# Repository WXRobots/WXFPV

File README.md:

# WXFPV
A FPV project for BF &amp; INAV

It include 2 parts for now：
Core Board and Main Board

## Core Board

Core Board is an exchangeable part to apply different MCUs for your ESC，such as AT32F421G8U7，EFM8BB21F16I etc.
The size of this circuit board is fully compatible with mtbsk8's design.
(https://oshwhub.com/mtbsk8/ji-yu-blheli-gu-jian-de-si-he-yi-wu-shua-dian-ji-dian-diao-esc-30-5mm-ban-ben)

EFM8BB21F16I's version can use BLHeli_S firmware
AT32F421G8U7's version can use AM32 firmare

## Main Board

Main Board is an 2-in-1 board，it include a flight controller and a 4-in-1 ESC in One Board.
It is designed to allow for splitting into two pieces for use,for better flexibility,replaceability and maintainability
It can use STM32F405RGT6 or APM32F405RGT6

It is additionally designed with 2 servo PWM interfaces and 3 high-power LED interfaces，so you can connect your servo or filament(or anything you want)to it

In the next upgrade,it will be 3-in-1，added by a communication module

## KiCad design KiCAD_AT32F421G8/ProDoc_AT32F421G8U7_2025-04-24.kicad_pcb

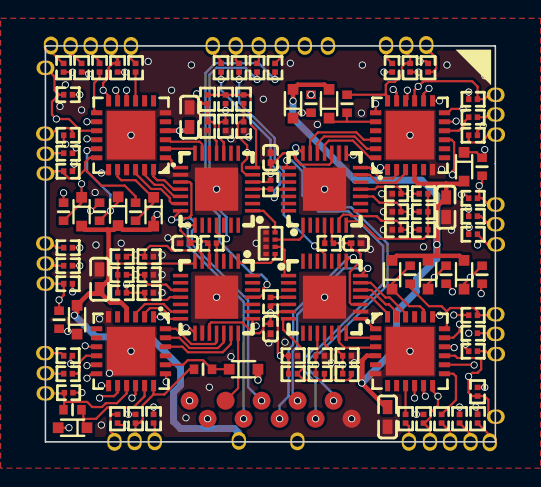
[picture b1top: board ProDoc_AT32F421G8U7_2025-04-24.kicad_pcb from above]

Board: 4 copper layers, 25.0 x 22.0 mm, 119 parts (0 on the bottom side), 111 nets.

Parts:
C1, C6, C11, C16: C0201
C3, C4, C5, C8, C9, C10, C13, C14, C15, C18, C19, C20, C29, C30, C31, C32: C0402
D1, D2, D3, D4, D5, D6, D7, D8, D9, D10, D11, D12: SOD-523_L1.2-W0.8-LS1.6-FD
R1, R4, R5, R6, R7, R8, R9, R10, R11, R12, R13, R14, R15, R16, R17, R18, R19, R21, R23, R24, R25, R26, R27, R28, R29, R30, R31, R32, R33, R34, R35, R36, R37, R39, R41, R42, R43, R44, R45, R46, R47, R48, R49, R50, R51, R52, R53, R54, R55, R58, R59, R60, R61, R62, R63, R64, R65, R66, R67, R68, R69, R70, R71, R72, R73, R74, R75, R76: R0201
RN1: RES-ARRAY-SMD_0201-8P-L1.4-W0.6-BL
TP1, TP2, TP3, TP4, TP5, TP6, TP7, TP8, TP9, TP10: Test-Point-0.5mm
U1, U3, U5, U7: VQFN-24_L4.0-W4.0-P0.50-TL-EP2.7
U2, U4, U6, U8: QFN-28_L4.0-W4.0-P0.40-TL-EP2.4

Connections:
3.3V: C1.2, C6.2, C11.2, C16.2, R73.1, R74.1, R75.1, R76.1, TP10.1, U2.5, U2.17, U4.5, U4.17, U6.5, U6.17, U8.5, U8.17
12V: C29.2, C30.2, C31.2, C32.2, D1.1, D2.1, D3.1, D4.1, D5.1, D6.1, D7.1, D8.1, D9.1, D10.1, D11.1, D12.1, U1.4, U3.4, U5.4, U7.4
$1N5017: R1.1, U2.25
$1N5688: R73.2, U2.4
$2N3149: R19.1, U4.25
$2N3240: R74.2, U4.4
$3N2377: R37.1, U6.25
$3N3106: R75.2, U6.4
$4N2377: R55.1, U8.25
$4N3105: R76.2, U8.4
BOOT1: RN1.5, U2.1
BOOT2: RN1.8, U4.1
BOOT3: RN1.6, U6.1
BOOT4: RN1.7, U8.1
GND: C1.1, C6.1, C11.1, C16.1, C29.1, C30.1, C31.1, C32.1, R16.1, R17.1, R18.1, R34.1, R35.1, R36.1, R52.1, R53.1, R54.1, R70.1, R71.1, R72.1, RN1.1, RN1.2, RN1.3, RN1.4, TP9.1, U1.6, U1.25, U2.16, U2.29, U3.6, U3.25, U4.16, U4.29, U5.6, U5.25, U6.16, U6.29, U7.6, U7.25, U8.16, U8.29
M1_AH: U1.22, U2.20
M1_AL: U1.1, U2.15
M1_BH: U1.23, U2.19
M1_BL: U1.2, U2.14
M1_CH: U1.24, U2.18
M1_CL: U1.3, U2.13
M1_HO1: R4.1, U1.19
M1_HO2: R5.1, U1.16
M1_HO3: R6.1, U1.13
M1_LO1: R7.1, U1.11
M1_LO2: R10.1, U1.10
M1_LO3: R15.1, U1.9
M1_SEN_A: R8.2, R9.1, R18.2, U2.6
M1_SEN_B: R11.2, R12.1, R17.2, U2.10
M1_SEN_C: R13.2, R14.1, R16.2, U2.11
M1_SEN_COM: R8.1, R11.1, R13.1, U2.7
M1_SWCLK: TP1.1, U2.22
M1_SWDIO: TP2.1, U2.21
M1_VB1: C3.1, D1.2, U1.20
M1_VB2: C4.1, D2.2, U1.17
M1_VB3: C5.1, D3.2, U1.14
M1_VS1: C3.2, R9.2, U1.18
M1_VS2: C4.2, R12.2, U1.15
M1_VS3: C5.2, R14.2, U1.12
M2_AH: U3.22, U4.20
M2_AL: U3.1, U4.15
M2_BH: U3.23, U4.19
M2_BL: U3.2, U4.14
M2_CH: U3.24, U4.18
M2_CL: U3.3, U4.13
M2_HO1: R21.1, U3.19
M2_HO2: R23.1, U3.16
M2_HO3: R24.1, U3.13
M2_LO1: R25.1, U3.11
M2_LO2: R26.1, U3.10
M2_LO3: R29.1, U3.9
M2_SEN_A: R27.2, R28.1, R36.2, U4.6
M2_SEN_B: R30.2, R31.1, R35.2, U4.10
M2_SEN_C: R32.2, R33.1, R34.2, U4.11
M2_SEN_COM: R27.1, R30.1, R32.1, U4.7
M2_SWCLK: TP3.1, U4.22
M2_SWDIO: TP4.1, U4.21
M2_VB1: C8.1, D4.2, U3.20
M2_VB2: C9.1, D5.2, U3.17
M2_VB3: C10.1, D6.2, U3.14
M2_VS1: C8.2, R28.2, U3.18
M2_VS2: C9.2, R31.2, U3.15
M2_VS3: C10.2, R33.2, U3.12
M3_AH: U5.22, U6.20
M3_AL: U5.1, U6.15
M3_BH: U5.23, U6.19
M3_BL: U5.2, U6.14
M3_CH: U5.24, U6.18
M3_CL: U5.3, U6.13
M3_HO1: R39.1, U5.19
M3_HO2: R41.1, U5.16
M3_HO3: R42.1, U5.13
M3_LO1: R43.1, U5.11
M3_LO2: R44.1, U5.10
M3_LO3: R49.1, U5.9
M3_SEN_A: R45.2, R46.1, R54.2, U6.6
M3_SEN_B: R47.2, R48.1, R53.2, U6.10
M3_SEN_C: R50.2, R51.1, R52.2, U6.11
M3_SEN_COM: R45.1, R47.1, R50.1, U6.7
M3_SWCLK: TP5.1, U6.22
M3_SWDIO: TP6.1, U6.21
M3_VB1: C13.1, D7.2, U5.20
M3_VB2: C14.1, D8.2, U5.17
M3_VB3: C15.1, D9.2, U5.14
M3_VS1: C13.2, R46.2, U5.18
M3_VS2: C14.2, R48.2, U5.15
M3_VS3: C15.2, R51.2, U5.12
M4_AH: U7.22, U8.20
M4_AL: U7.1, U8.15
M4_BH: U7.23, U8.19
M4_BL: U7.2, U8.14
M4_CH: U7.24, U8.18
M4_CL: U7.3, U8.13
M4_HO1: R58.1, U7.19
M4_HO2: R59.1, U7.16
M4_HO3: R60.1, U7.13
M4_LO1: R61.1, U7.11
M4_LO2: R62.1, U7.10
M4_LO3: R67.1, U7.9
M4_SEN_A: R63.2, R64.1, R72.2, U8.6
M4_SEN_B: R65.2, R66.1, R71.2, U8.10
M4_SEN_C: R68.2, R69.1, R70.2, U8.11
M4_SEN_COM: R63.1, R65.1, R68.1, U8.7
M4_SWCLK: TP7.1, U8.22
M4_SWDIO: TP8.1, U8.21
M4_VB1: C18.1, D10.2, U7.20
M4_VB2: C19.1, D11.2, U7.17
M4_VB3: C20.1, D12.2, U7.14
M4_VS1: C18.2, R64.2, U7.18
M4_VS2: C19.2, R66.2, U7.15
M4_VS3: C20.2, R69.2, U7.12

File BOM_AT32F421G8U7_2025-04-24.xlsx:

No. | Quantity | Comment | Designator | Footprint | Value | Manufacturer Part | Manufacturer | Supplier Part | Supplier
1 | 4 | 100nF | C1,C6,C11,C16 | C0201 | 100nF | GRM033R61E104KE14D | muRata(村田) | C76939 | LCSC
2 | 12 | 1uF | C3,C4,C5,C8,C9,C10,C13,C14,C15,C18,C19,C20 | C0402 | 1uF | CL05A105KA5NQNC | SAMSUNG(三星) | C52923 | LCSC
3 | 4 | 4.7uF | C29,C30,C31,C32 | C0402 | 4.7uF | CGA0402X5R475M250GT | HRE(芯声) | C6119795 | LCSC
4 | 12 | 1N4148WT | D1,D2,D3,D4,D5,D6,D7,D8,D9,D10,D11,D12 | SOD-523_L1.2-W0.8-LS1.6-FD |  | 1N4148WT | WPMtek(维攀微) | C2688234 | LCSC
5 | 4 | 220Ω | R1,R19,R37,R55 | R0201 | 220Ω | RC0201FR-07220RL | YAGEO(国巨) | C274342 | LCSC
6 | 24 | 4.7Ω | R4,R5,R6,R7,R10,R15,R21,R23,R24,R25,R26,R29,R39,R41,R42,R43,R44,R49,R58,R59,R60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 | R0201 | 4.7Ω | 0201WMJ047JTEE | UNI-ROYAL(厚声) | C473492 | LCSC
7 | 28 | 10kΩ | R8,R9,R11,R12,R13,R14,R27,R28,R30,R31,R32,R33,R45,R46,R47,R48,R50,R51,R63,R64,R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 | R0201 | 10kΩ | 0201WMF1002TEE | UNI-ROYAL(厚声) | C473048 | LCSC
8 | 12 | 1kΩ | R16,R17,R18,R34,R35,R36,R52,R53,R54,R70,R71,R72 | R0201 | 1kΩ | 0201WMF1001TEE | UNI-ROYAL(厚声) | C270365 | LCSC
9 | 1 | 10kΩ | RN1 | RES-ARRAY-SMD_0201-8P-L1.4-W0.6-BL | 10kΩ | 4F01WMJ0103TEE | UNI-ROYAL(厚声) | C2769814 | LCSC
10 | 10 | Test-Point | TP1,TP2,TP3,TP4,TP5,TP6,TP7,TP8,TP9,TP10 | Test-Point-0.5mm
11 | 4 | JSM6288Q | U1,U3,U5,U7 | VQFN-24_L4.0-W4.0-P0.50-TL-EP2.7 |  | JSM6288Q | JSMSEMI(杰盛微) | C19077370 | LCSC
12 | 4 | AT32F421G8U7 | U2,U4,U6,U8 | QFN-28_L4.0-W4.0-P0.40-TL-EP2.4 |  | AT32F421G8U7 | ARTERY(雅特力) | C2765098 | LCSC

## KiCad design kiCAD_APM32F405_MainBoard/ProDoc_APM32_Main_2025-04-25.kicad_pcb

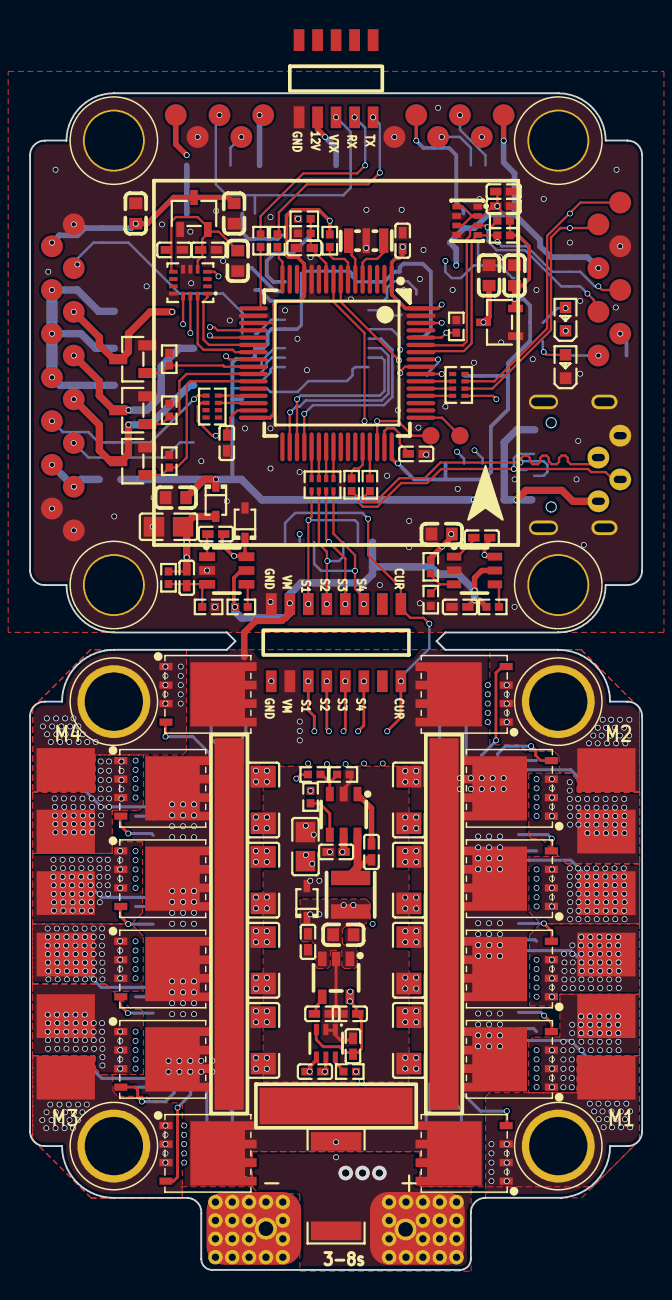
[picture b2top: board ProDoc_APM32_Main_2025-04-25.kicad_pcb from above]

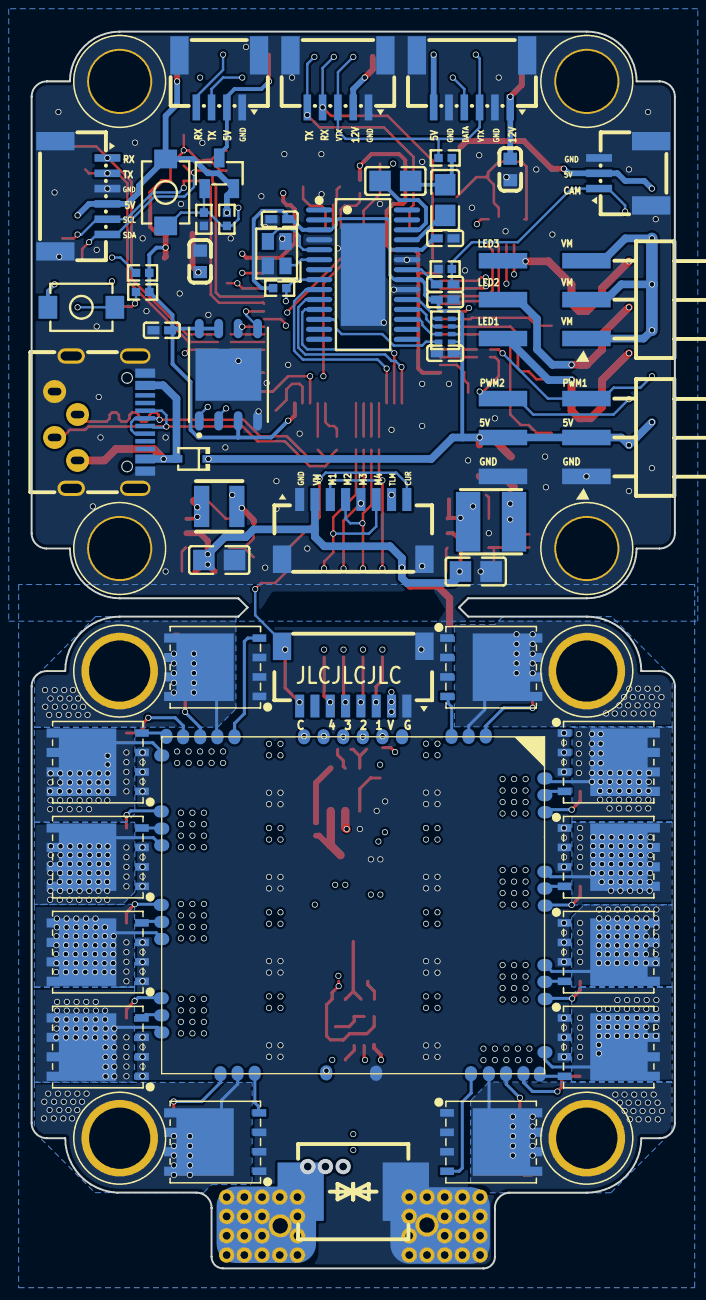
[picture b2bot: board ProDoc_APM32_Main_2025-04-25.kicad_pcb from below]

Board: 6 copper layers, 42.0 x 80.8 mm, 194 parts (59 on the bottom side), 136 nets.

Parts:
AT7456E1: TSSOP-28_L9.7-W4.4-P0.65-LS6.4-BL-EP-2
C18, C19, C20, C27, C28, C29, C30, C32, C41, C44, C45, C48, C49, C50, C51, C52, C53, C54, C55, C56, C57, C58, C61, C63, C66: C0402
C33, C38, C40, C42, C43, C62, C68, C69, C78, C79: C0603
C46, C47, C60, C64, C65, C67: C0805
C70, C71, C72, C73, C74, C75, C76, C77: C1206
CN1, CN2: CONN-SMD_8P-P1.00_MXSH-1.0-08P-WT1-0-A
D1, D2, D6: SOD-323_L1.7-W1.3-LS2.5-FD
D3: SOD-323_L1.7-W1.3-LS2.7-RD
H1: HDR-SMD_8P_P1.27-跨板连接排针
H2: HDR-SMD_5P_P1.27-跨板连接排针
L1, L2: IND-SMD_L3.0-W3.0-1
L3: IND-SMD_L4.0-W4.0_FNR40XXS
LED1, LED2: LED0603-RD
Q1, Q2, Q3, Q4, Q5, Q6, Q7, Q8, Q9, Q10, Q11, Q12, Q13, Q14, Q15, Q16, Q17, Q18, Q19, Q20, Q21, Q22, Q23, Q24: TDSON-8_L5.9-W5.2-P1.27-BL
Q25, Q26, Q56, Q57: SOT-23-3_L2.9-W1.3-P1.90-LS2.4-BR
R1, R2, R3, R4, R5, R6, R10, R11, R12, R13, R14, R15, R16, R17, R18, R19, R20, R28, R29, R30, R31, R108, R109, R110, R111, R112, R113, R114, R115, R116: R0402
RN1, RN2, RN3, RN4: RES-ARRAY-SMD_0402-8P-L2.0-W1.0-BL
SW1, SW2: KEY-SMD_L3.9-W3.0-LS5.0
TP1, TP2, TP3, TP4, TP5, TP6, TP7, TP8, TP10, TP12, TP14, TP16, TP17, TP19, TP20, TP21, TP22, TP23, TP24, TP25, TP26, TP27, TP29, TP30, TP31, TP32, TP33, TP34, TP35, TP36, TP38, TP40, TP41, TP42, TP43, TP44, TP45, TP46, TP47, TP48: Test-Point-0.5mm
U1: SC-70-6_L2.2-W1.3-P0.65-LS2.1-TL
U2: R2512
U3: LQFP-64_L10.0-W10.0-P0.50-LS12.0-BL
U4: SOT-23-5_L3.0-W1.7-P0.95-LS2.8-BR
U6, U55, U56: SOT-23-6_L2.9-W1.6-P0.95-LS2.8-BR
U8: BLHeli_四合一核心板_SJJ
U9: SMC_L6.9-W5.9-LS7.9-BI
U10, U11: SOT-23-3_L3.0-W1.7-P0.95-LS2.9-BR
U12: LGA-14_L3.0-W2.5-P0.50-BR
U13: OSC-SMD_4P-L2.0-W1.6-BL_X201624MKB4SI
U14: LGA-8_L2.5-W2.0-P0.65_AMP6127
U15: WSON-8_L6.0-W5.0-P1.27-BL-EP
U16, U54: CONN-SMD_6P-P1.00_MEGASTAR_ZX-SH1.0-6PWT
U17: CONN-SMD_5P-P1.00_MEGASTAR_ZX-SH1.0-5PWT
U18: CONN-SMD_3P-P1.00_MEGASTAR_ZX-SH1.0-3PWT
U19, U57: HDR-SMD_6P-P2.54-H-M-R2-C3-LS17.0
U53: CONN-SMD_4P-P1.00_MEGASTAR_ZX-SH1.0-4PWT
U58, U59: SMD-1_L25.0-W1.5
U60: SMD-2_L10.0-W2.0
USBC1: USB-C-SMD_KH-TYPE-C-16P
X1: OSC-SMD_3P-L3.2-W1.3-P1.2-L

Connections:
3V3: C27.1, C38.2, C48.1, C49.1, C51.1, R1.2, R2.2, R3.2, R4.2, R6.2, SW1.2, TP8.1, U3.1, U3.13, U3.19, U3.32, U3.48, U3.64, U10.2, U14.2, U14.6, U14.8, U15.3, U15.7, U15.8
3V3_GYRO: C43.2, C52.2, C53.2, U11.2, U12.5, U12.8
5V: AT7456E1.3, AT7456E1.21, AT7456E1.24, C40.2, C42.2, C54.2, C55.2, C56.2, C57.2, C68.2, C69.2, C78.2, D1.2, D2.2, Q56.2, R17.2, R108.2, RN4.5, RN4.6, RN4.7, RN4.8, SW2.1, TP16.1, TP20.1, TP24.1, TP26.1, TP29.1, U10.3, U11.3, U16.4, U18.2, U19.3, U19.4
12V: C28.2, C33.2, D3.1, L1.2, R30.2, U4.1, U4.3, U8.14
$1N5871: C20.1, U6.1
$1N5872: R29.2, U6.4
$1N5875: R30.1, R31.2, U6.3
$1N5876: C20.2, L1.1, U6.6
$1N5882: C29.2, U4.4
$3N1830: R28.1, U1.6
$4N5037: R6.1, U3.7
$4N5056: C45.1, U3.31
$4N5066: C41.1, U3.47
$4N5110: AT7456E1.6, U13.1
$4N5111: AT7456E1.5, U13.3
$4N5116: AT7456E1.22, C50.2
$4N5118: C46.2, C47.2, R16.1
$4N5119: AT7456E1.25, C47.1
$4N5120: AT7456E1.26, C46.1
$4N5162: LED2.2, R4.1
$4N5163: LED1.2, R1.1
$4N5203: RN1.3, U3.54
$4N5204: RN1.2, U3.53
$4N5218: R10.1, U3.16
$4N5219: R11.1, U3.17
$4N5327: AT7456E1.12, RN4.1
$4N5328: AT7456E1.17, RN4.2
$4N5329: AT7456E1.18, RN4.3
$4N5330: AT7456E1.19, RN4.4
$4N14776: C58.1, U55.1
$4N14777: R110.2, U55.4
$4N14780: R111.2, R112.1, U55.3
$4N14781: C58.2, L2.1, U55.6
$4N15508: C63.2, D6.2, L3.1, U56.6
$4N15513: C63.1, U56.1
$4N15879: R113.2, U56.4
$4N16265: C66.1, R114.2, R115.1, U56.3
+3.3V: C18.1, C30.2, U1.3, U4.5, U8.35
ADC_CUR: CN1.8, CN1.9, CN2.8, H1.1, R28.2, U3.9
ADC_VBAT: C44.1, R14.1, R15.2, U3.10
AH_1: Q1.4, U8.11
AH_2: Q7.4, U8.2
AH_3: Q13.4, U8.22
AH_4: Q19.4, U8.31
AL_1: Q2.4, U8.13
AL_2: Q8.4, U8.3
AL_3: Q14.4, U8.23
AL_4: Q20.4, U8.33
A_1: Q1.1, Q1.2, Q1.3, Q2.5, U8.12
A_2: Q7.1, Q7.2, Q7.3, Q8.5, U8.4
A_3: Q13.1, Q13.2, Q13.3, Q14.5, U8.24
A_4: Q19.1, Q19.2, Q19.3, Q20.5, U8.32
BH_1: Q3.4, U8.8
BH_2: Q9.4, U8.43
BH_3: Q15.4, U8.19
BH_4: Q21.4, U8.28
BIND: Q56.1, R108.1, R109.2, SW2.2, TP34.1
BL_1: Q4.4, U8.9
BL_2: Q10.4, U8.44
BL_3: Q16.4, U8.20
BL_4: Q22.4, U8.29
BOOT0: R5.1, SW1.1, TP7.1, U3.60
BOX_CS: U3.8, U15.1
BOX_MISO: U3.56, U15.2
BOX_MOSI: U3.57, U15.5
BOX_SCK: U3.55, U15.6
B_1: Q3.1, Q3.2, Q3.3, Q4.5, U8.10
B_2: Q9.1, Q9.2, Q9.3, Q10.5, U8.1
B_3: Q15.1, Q15.2, Q15.3, Q16.5, U8.21
B_4: Q21.1, Q21.2, Q21.3, Q22.5, U8.30
CAM: C50.1, R18.2, TP22.1, U18.1
CH_1: Q5.4, U8.5
CH_2: Q11.4, U8.42
CH_3: Q17.4, U8.18
CH_4: Q23.4, U8.25
CL_1: Q6.4, U8.6
CL_2: Q12.4, U8.40
CL_3: Q18.4, U8.16
CL_4: Q24.4, U8.26
C_1: Q5.1, Q5.2, Q5.3, Q6.5, U8.7
C_2: Q11.1, Q11.2, Q11.3, Q12.5, U8.41
C_3: Q17.1, Q17.2, Q17.3, Q18.5, U8.17
C_4: Q23.1, Q23.2, Q23.3, Q24.5, U8.27
D+: R13.2, TP5.1, USBC1.A6, USBC1.B6
D-: R12.2, TP3.1, USBC1.A7, USBC1.B7
DC_5V: C65.1, C66.2, D2.1, L3.2, R115.2
DM: R12.1, U3.44
DP: R13.1, U3.45
ELRS_5V: Q56.3, TP31.1, U53.2
ESC_S1: CN1.3, CN2.3, H1.6, RN2.8, U8.38
ESC_S2: CN1.4, CN2.4, H1.5, RN2.7, U8.39
ESC_S3: CN1.5, CN2.5, H1.4, RN2.6, U8.36
ESC_S4: CN1.6, CN2.6, H1.3, RN2.5, U8.37
GND: AT7456E1.4, AT7456E1.20, AT7456E1.23, AT7456E1.29, C18.2, C27.2, C28.1, C29.1, C30.1, C32.1, C33.1, C38.1, C40.1, C41.2, C42.1, C43.1, C44.2, C45.2, C48.2, C49.2, C51.2, C52.1, C53.1, C54.1, C55.1, C56.1, C57.1, C60.1, C61.1, C62.1, C64.1, C65.2, C67.1, C68.1, C69.1, C70.1, C71.1, C72.1, C73.1, C74.1, C75.1, C76.1, C77.1, C78.1, C79.1, CN1.1, CN1.10, CN2.1, CN2.9, CN2.10, D3.2, D6.1, H1.8, H2.1, LED1.1, Q2.1, Q2.2, Q2.3, Q4.1, Q4.2, Q4.3, Q6.1, Q6.2, Q6.3, Q8.1, Q8.2, Q8.3, Q10.1, Q10.2, Q10.3, Q12.1, Q12.2, Q12.3, Q14.1, Q14.2, Q14.3, Q16.1, Q16.2, Q16.3, Q18.1, Q18.2, Q18.3, Q20.1, Q20.2, Q20.3, Q22.1, Q22.2, Q22.3, Q24.1, Q24.2, Q24.3, Q25.2, Q26.2, Q57.2, R5.2, R15.1, R18.1, R19.1, R20.1, R31.1, R109.1, R111.1, R114.1, R116.1, TP6.1, TP14.1, TP17.1, TP23.1, TP30.1, TP35.1, TP46.1, U1.1, U1.2, U3.12, U3.18, U3.63, U4.2, U6.2, U8.15, U9.1, U10.1, U11.1, U12.6, U12.7, U12.11, U13.2, U13.4, U14.1, U14.5, U14.7, U15.4, U15.9, U16.3, U16.7, U16.8, U17.1, U17.6, U17.7, U18.3, U18.4, U18.5, U19.1, U19.2, U53.1, U53.5, U53.6, U54.2, U54.5, U54.7, U54.8, U55.2, U56.2, USBC1.1, USBC1.2, USBC1.3, USBC1.4, USBC1.A1, USBC1.A12, USBC1.B1, USBC1.B12, X1.2
GYRO1_CS: U3.20, U12.12
GYRO1_EXTI: U3.24, U12.4
I2C1_SCL: R2.1, TP19.1, U3.58, U14.4, U16.5
I2C1_SDA: R3.1, TP21.1, U3.59, U14.3, U16.6
LED: LED2.1, U3.62
LED1_GATE: Q25.1, R19.2, U3.27
LED1_OUT: Q25.3, TP42.1, U57.2
LED2_GATE: Q26.1, R20.2, U3.26
LED2_OUT: Q26.3, TP43.1, U57.4
LED3_GATE: Q57.1, R116.2, U3.25
LED3_OUT: Q57.3, TP44.1, U57.6
MOTOR1: RN2.1, U3.37
MOTOR2: RN2.2, U3.38
MOTOR3: RN2.3, U3.39
MOTOR4: RN2.4, U3.40
MOTOR7: RN3.5, U3.29
MOTOR8: RN3.6, U3.30
OSC_IN: U3.5, X1.3
OSC_OUT: U3.6, X1.1
OSD_CS: AT7456E1.8, R17.1, TP4.1, U3.46
PWM1: RN3.4, TP25.1, U19.5
PWM2: RN3.3, TP27.1, U19.6
SPI1_SCK: U3.21, U12.13
SPI1_SDI: U3.22, U12.1
SPI1_SDO: U3.23, U12.14
SPI2_SCK: AT7456E1.10, U3.34
SPI2_SDI: AT7456E1.11, U3.35
SPI2_SDO: AT7456E1.9, U3.36
SWCLK: TP1.1, U3.49
TLM: CN2.7, RN1.8
UART2_RX: H2.4, R11.2, TP33.1, U17.4, U53.4
UART2_TX: H2.5, R10.2, TP32.1, U17.5, U53.3
UART3_RX: RN1.1, U3.52
UART5_RX: RN1.6, TP10.1, U16.1
UART5_TX: RN1.7, TP12.1, U16.2
USB_5V: D1.1, TP2.1, USBC1.A4, USBC1.A9, USBC1.B4, USBC1.B9
VBAT: C19.1, U1.4, U2.1, U9.2
VM: C19.2, C32.2, C60.2, C61.2, C64.2, C67.2, C70.2, C71.2, C72.2, C73.2, C74.2, C75.2, C76.2, C77.2, CN1.2, CN2.2, H1.7, Q1.5, Q3.5, Q5.5, Q7.5, Q9.5, Q11.5, Q13.5, Q15.5, Q17.5, Q19.5, Q21.5, Q23.5, R14.2, R29.1, R110.1, R113.1, TP45.1, TP47.1, TP48.1, U1.5, U2.2, U6.5, U55.5, U56.5, U57.1, U57.3, U57.5, U58.1, U59.1, U60.1
VTX: H2.3, R16.2, TP38.1, U17.3, U54.3
VTX_5VOUT: TP40.1, U54.6
VTX_12V: C62.2, C79.2, H2.2, L2.2, R112.2, TP41.1, U17.2, U54.1
VTX_RX: TP36.1, U54.4

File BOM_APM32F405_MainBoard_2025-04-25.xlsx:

No. | Quantity | Comment | Designator | Footprint | Value | Manufacturer Part | Manufacturer | Supplier Part | Supplier
1 | 1 | AT7456E | AT7456E1 | TSSOP-28_L9.7-W4.4-P0.65-LS6.4-BL-EP-2 |  | AT7456E | 杭州中科微 | C82351 | LCSC
2 | 17 | 100nF | C18,C20,C27,C32,C44,C48,C49,C50,C51,C53,C54,C55,C56,C57,C58,C61,C63 | C0402 | 100nF | CL05B104KB54PNC | SAMSUNG(三星) | C307331 | LCSC
3 | 1 | 1nF | C19 | C0402 | 1nF | 0402B102K500NT | FH(风华) | C1523 | LCSC
4 | 1 | 1uF | C28 | C0402 | 1uF | CL05A105KA5NQNC | SAMSUNG(三星) | C52923 | LCSC
5 | 1 | 100pF | C29 | C0402 | 100pF | 0402CG101J500NT | FH(风华) | C1546 | LCSC
6 | 3 | 2.2uF | C30,C41,C45 | C0402 | 2.2uF | CL05A225MQ5NSNC | SAMSUNG(三星) | C12530 | LCSC
7 | 7 | 10uF | C33,C38,C40,C42,C43,C62,C79 | C0603 | 10uF | CL10A106MA8NRNC | SAMSUNG(三星) | C96446 | LCSC
8 | 3 | 22uF | C46,C47,C65 | C0805 | 22uF | CL21A226MAQNNNE | SAMSUNG(三星) | C45783 | LCSC
9 | 1 | 10nF | C52 | C0402 | 10nF | CL05B103KB5NNNC | SAMSUNG(三星) | C15195 | LCSC
10 | 3 | 4.7uF | C60,C64,C67 | C0805 | 4.7uF | CL21A475KBQNNNE | SAMSUNG(三星) | C98192 | LCSC
11 | 1 | 22pF | C66 | C0402 | 22pF | 0402CG220J500NT | FH(风华) | C1555 | LCSC
12 | 3 | 10uF | C68,C69,C78 | C0603 | 10uF | CL10A106KP8NNNC | SAMSUNG(三星) | C19702 | LCSC
13 | 8 | 10uF | C70,C71,C72,C73,C74,C75,C76,C77 | C1206 | 10uF | CL31A106KBHNNNE | SAMSUNG(三星) | C13585 | LCSC
14 | 2 | MXSH-1.0-08P-WT1-0-A | CN1,CN2 | CONN-SMD_8P-P1.00_MXSH-1.0-08P-WT1-0-A |  | MXSH-1.0-08P-WT1-0-A | MAX(迈旭) | C19185711 | LCSC
15 | 3 | B5819WS | D1,D2,D6 | SOD-323_L1.7-W1.3-LS2.5-FD |  | B5819WS | 宏迦橙 | C7420331 | LCSC
16 | 1 | SD12 | D3 | SOD-323_L1.7-W1.3-LS2.7-RD |  | SD12 | MDD | C502528 | LCSC
17 | 1 | HDR-SMD_8P_P1.27_跨板连接排针 | H1 | HDR-SMD_8P_P1.27-跨板连接排针
18 | 1 | OPTO | H2 | HDR-SMD_5P_P1.27-跨板连接排针
19 | 2 | 10uH | L1,L2 | IND-SMD_L3.0-W3.0-1 | 10uH | CKCSA3010-10uH/M | CENKER(岑科) | C5125973 | LCSC
20 | 1 | 10uH | L3 | IND-SMD_L4.0-W4.0_FNR40XXS | 10uH | MAI4020S-100MT | ceaiya(柯爱亚) | C520273 | LCSC
21 | 1 | PWR | LED1 | LED0603-RD |  | KT-0603R | KENTO | C2286 | LCSC
22 | 1 | LED | LED2 | LED0603-RD |  | NCD0603Y1 | 国星光电 | C84268 | LCSC
23 | 24 | HYG011N04LS2C2 | Q1,Q2,Q3,Q4,Q5,Q6,Q7,Q8,Q9,Q10,Q11,Q12,Q13,Q14,Q15,Q16,Q17,Q18,Q19,Q20,Q21,Q22,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 | TDSON-8_L5.9-W5.2-P1.27-BL |  | HYG011N04LS2C2 |  | C9900088765 | LCSC
24 | 3 | AO3400A | Q25,Q26,Q57 | SOT-23-3_L2.9-W1.3-P1.90-LS2.4-BR |  | AO3400A | AOS | C20917 | LCSC
25 | 1 | HL3401A | Q56 | SOT-23-3_L2.9-W1.3-P1.90-LS2.4-BR |  | HL3401A | 宏嘉诚 | C7420349 | LCSC
26 | 4 | 1kΩ | R1,R4,R15,R109 | R0402 | 1kΩ | 0402WGF1001TCE | UNI-ROYAL(厚声) | C11702 | LCSC
27 | 2 | 4.7kΩ | R2,R3 | R0402 | 4.7kΩ | 0402WGF4701TCE | UNI-ROYAL(厚声) | C25900 | LCSC
28 | 7 | 10kΩ | R5,R6,R14,R17,R19,R20,R116 | R0402 | 10kΩ | 0402WGF1002TCE | UNI-ROYAL(厚声) | C25744 | LCSC
29 | 4 | 22Ω | R10,R11,R12,R13 | R0402 | 22Ω | 0402WGF220JTCE | UNI-ROYAL(厚声) | C25092 | LCSC
30 | 2 | 75Ω | R16,R18 | R0402 | 75Ω | 0402WGF750JTCE | UNI-ROYAL(厚声) | C25133 | LCSC
31 | 1 | 56Ω | R28 | R0402 | 56Ω | RC0402FR-0756RL | YAGEO(国巨) | C137957 | LCSC
32 | 3 | 100kΩ | R29,R110,R113 | R0402 | 100kΩ | TR0402D10K0Q1025Z | EVER OHMS(天二科技) | C149898 | LCSC
33 | 2 | 27kΩ | R30,R112 | R0402 | 27kΩ | 0402WGF2702TCE | UNI-ROYAL(厚声) | C25771 | LCSC
34 | 2 | 2kΩ | R31,R111 | R0402 | 2kΩ | 0402WGF2001TCE | UNI-ROYAL(厚声) | C4109 | LCSC
35 | 1 | 100kΩ | R108 | R0402 | 100kΩ | 0402WGF1003TCE | UNI-ROYAL(厚声) | C25741 | LCSC
36 | 1 | 6.8kΩ | R114 | R0402 | 6.8kΩ | 0402WGF6801TCE | UNI-ROYAL(厚声) | C25917 | LCSC
37 | 1 | 51kΩ | R115 | R0402 | 51kΩ | 0402WGF5102TCE | UNI-ROYAL(厚声) | C25794 | LCSC
38 | 3 | 22Ω | RN1,RN2,RN3 | RES-ARRAY-SMD_0402-8P-L2.0-W1.0-BL | 22Ω | 4D02WGJ0220TCE | UNI-ROYAL(厚声) | C25499 | LCSC
39 | 1 | 1kΩ | RN4 | RES-ARRAY-SMD_0402-8P-L2.0-W1.0-BL | 1kΩ | 4D02WGJ0102TCE | UNI-ROYAL(厚声) | C25726 | LCSC
40 | 1 | Boot | SW1 | KEY-SMD_L3.9-W3.0-LS5.0 |  | BX-TS-26-3929325T | Bossie(博锡) | C18077675 | LCSC
41 | 1 | Bind | SW2 | KEY-SMD_L3.9-W3.0-LS5.0 |  | BX-TS-26-3929325T | Bossie(博锡) | C18077675 | LCSC
42 | 8 | Test-Point | TP1,TP2,TP3,TP4,TP5,TP6,TP7,TP8 | Test-Point-0.5mm
43 | 1 | UART5_RX | TP10 | Test-Point-0.5mm
44 | 1 | UART5_TX | TP12 | Test-Point-0.5mm
45 | 6 | GND | TP14,TP17,TP23,TP30,TP35,TP46 | Test-Point-0.5mm
46 | 6 | 5V | TP16,TP20,TP24,TP26,TP29,TP40 | Test-Point-0.5mm
47 | 1 | SCL | TP19 | Test-Point-0.5mm
48 | 1 | SDA | TP21 | Test-Point-0.5mm
49 | 1 | CAM | TP22 | Test-Point-0.5mm
50 | 1 | PWM1 | TP25 | Test-Point-0.5mm
51 | 1 | PWM2 | TP27 | Test-Point-0.5mm
52 | 1 | ELRS_5V | TP31 | Test-Point-0.5mm
53 | 1 | TX | TP32 | Test-Point-0.5mm
54 | 2 | RX | TP33,TP36 | Test-Point-0.5mm
55 | 1 | Bind | TP34 | Test-Point-0.5mm
56 | 1 | VTX | TP38 | Test-Point-0.5mm
57 | 1 | 12V | TP41 | Test-Point-0.5mm
58 | 1 | LED1 | TP42 | Test-Point-0.5mm
59 | 1 | LED2 | TP43 | Test-Point-0.5mm
60 | 1 | LED3 | TP44 | Test-Point-0.5mm
61 | 3 | VM | TP45,TP47,TP48 | Test-Point-0.5mm
62 | 1 | TP181A2-CR | U1 | SC-70-6_L2.2-W1.3-P0.65-LS2.1-TL |  | TP181A2-CR | 3PEAK(思瑞浦) | C2902350 | LCSC
63 | 1 | 0.5mΩ | U2 | R2512 | 0.5mΩ | EBWM2512FL500S9 | RESI(开步睿思) | C7178835 | LCSC
64 | 1 | APM32F405RGT6 | U3 | LQFP-64_L10.0-W10.0-P0.50-LS12.0-BL |  | APM32F405RGT6 | Geehy(珠海极海) | C5290473 | LCSC
65 | 1 | AP2210K-3.3TRG1 | U4 | SOT-23-5_L3.0-W1.7-P0.95-LS2.8-BR |  | AP2210K-3.3TRG1 | DIODES(美台) | C176959 | LCSC
66 | 2 | JW5026 | U6,U55 | SOT-23-6_L2.9-W1.6-P0.95-LS2.8-BR |  | JW5026 | Joulwatt(杰华特) | C185109 | LCSC
67 | 1 | BLHeli四合一核心板_SJJ | U8 | BLHeli_四合一核心板_SJJ
68 | 1 | SMDJ28CA | U9 | SMC_L6.9-W5.9-LS7.9-BI |  | SMDJ28CA | Liown(里阳半导体) | C2990249 | LCSC
69 | 2 | XC6206P332MR | U10,U11 | SOT-23-3_L3.0-W1.7-P0.95-LS2.9-BR |  | XC6206P332MR | UMW(友台半导体) | C347376 | LCSC
70 | 1 | BMI270 | U12 | LGA-14_L3.0-W2.5-P0.50-BR |  | BMI270 | Bosch(博世) | C2836813 | LCSC
71 | 1 | 27MHz | U13 | OSC-SMD_4P-L2.0-W1.6-BL_X201624MKB4SI | 27MHz | X201627MOB4SI | YXC(扬兴晶振) | C5210654 | LCSC
72 | 1 | BMP280 | U14 | LGA-8_L2.5-W2.0-P0.65_AMP6127 |  | BMP280 | Bosch(博世) | C83291 | LCSC
73 | 1 | W25Q128JVPIQ | U15 | WSON-8_L6.0-W5.0-P1.27-BL-EP |  | W25Q128JVPIQ | WINBOND(华邦) | C190862 | LCSC
74 | 1 | GPS | U16 | CONN-SMD_6P-P1.00_MEGASTAR_ZX-SH1.0-6PWT |  | ZX-SH1.0-6PWT | Megastar(兆星) | C7430448 | LCSC
75 | 1 | Opt | U17 | CONN-SMD_5P-P1.00_MEGASTAR_ZX-SH1.0-5PWT |  | ZX-SH1.0-5PWT | Megastar(兆星) | C7430447 | LCSC
76 | 1 | CAM | U18 | CONN-SMD_3P-P1.00_MEGASTAR_ZX-SH1.0-3PWT |  | ZX-SH1.0-3PWT | Megastar(兆星) | C7430445 | LCSC
77 | 1 | SERVO | U19 | HDR-SMD_6P-P2.54-H-M-R2-C3-LS17.0 |  | PZ254-2-03-WS | HCTL(华灿天禄) | C5149353 | LCSC
78 | 1 | ELRS | U53 | CONN-SMD_4P-P1.00_MEGASTAR_ZX-SH1.0-4PWT |  | ZX-SH1.0-4PWT | Megastar(兆星) | C7430446 | LCSC
79 | 1 | VTX | U54 | CONN-SMD_6P-P1.00_MEGASTAR_ZX-SH1.0-6PWT |  | ZX-SH1.0-6PWT | Megastar(兆星) | C7430448 | LCSC
80 | 1 | SY8292ABC | U56 | SOT-23-6_L2.9-W1.6-P0.95-LS2.8-BR |  | SY8292ABC | silergy(矽力杰) | C83336 | LCSC
81 | 1 | LED | U57 | HDR-SMD_6P-P2.54-H-M-R2-C3-LS17.0 |  | PZ254-2-03-WS | HCTL(华灿天禄) | C5149353 | LCSC
82 | 2 | STHW4-DU-HN2501X510 | U58,U59 | SMD-1_L25.0-W1.5 |  | STHW4-DU-HN2501X510 | STEIPU(斯泰普) | C18548290 | LCSC
83 | 1 | BTC-1022-BN01 | U60 | SMD-2_L10.0-W2.0 |  | BTC-1022-BN01 | BZXC(博众新材) | C20883043 | LCSC
84 | 1 | KH-TYPE-C-16P | USBC1 | USB-C-SMD_KH-TYPE-C-16P |  | KH-TYPE-C-16P | kinghelm(金航标) | C709357 | LCSC
85 | 1 | 8MHz | X1 | OSC-SMD_3P-L3.2-W1.3-P1.2-L | 8MHz | CSTCE8M00G15C99-R0 | muRata(村田) | C110614 | LCSC
